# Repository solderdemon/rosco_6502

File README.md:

# Really Old-School Computer - 6502

## A 65C02 Single-Board Computer

This repository holds design files, firmware and software for the Really Old-School Computer
(6502) single-board computer, AKA the rosco_6502. This is a fully-featured, programmable,
extensible and capable 8-bit retro computer that is completely open source.

The rosco_6502 is the "little brother" of the popular [rosco_m68k](https://github.com/rosco-m68k)
m68k computer. It is made by the same people, and shares the ethos of being powerful, extensible
and above all, fun.

This project contains all the design files and source code for the project.

* All Software released under the MIT licence. See LICENSE for details.
* All Hardware released under the CERN Open Hardware licence. See LICENCE.hardware.txt.
* All Documentation released under Creative Commons Attribution. See <https://creativecommons.org/licenses/by/2.0/uk/>

## Documentation

Start with the [documentation index](docs/README.md).

* [Getting started and terminal setup](docs/getting-started.md)
* [Hardware and memory map](docs/hardware.md)
* [Building and programming ROM](docs/rom-firmware.md)
* [Building and programming PLDs](docs/pld-firmware.md)
* [Developing and loading programs](docs/software.md)
* [Troubleshooting](docs/troubleshooting.md)
* [Revision 4 notes](docs/revision-4.md)

## Specifications

### Hardware

The hardware specifications for the rosco_6502 are:

* WDC 65C02 at up-to 14MHz (In theory, 10MHz testing target currently).
* SCN68681C1A44 provides two UARTs, timers and SD Card / SPI / GPIO; the console runs at 38400 bit/s
* 528KB RAM
  * 16KB low RAM ($0000 - $3FFF)
  * 16 x 32KB RAM banks ($4000 - $BFFF)
* 8KB IO space ($C000 - $DFFF)
* 8KB or 32KB (banked) ROM $E000 - $FFFF
* High-speed decode and glue logic handled by Atmel F22V10C PLDs.
* Comprehensive expansion and IO connectors allow the system to be easily expanded!

You can see the electrical designs in [kicad](design/kicad). Programmable logic lives in [pld](code/pld).

### Software

The current firmware uses the cc65 toolchain (`ca65`, `ld65` and `da65`).
It includes hardware initialization, WozMon, SD card access, read-only FAT32
support and boot code that looks for `/ROSC0DE_6502.BIN` on the SD card.
The firmware and filesystem utilities are still under development.

See the [firmware README](code/firmware/README.md) for build
instructions.

### Related tools

* [rosco CLI](https://github.com/solderdemon/rosco-cli): a cross-platform `rosco` command
  that creates, builds and uploads rosco_6502 (and rosco_m68k) programs over UART, or
  runs them in the emulator.
* [rosco-emulator](https://github.com/solderdemon/rosco-emulator): a slimmed-down MAME
  build that emulates the rosco_6502 r4, so programs and firmware can be tested without
  the board.

See [Developing and loading programs](docs/software.md#rosco-cli-and-emulator) for usage.

## Repository layout

* [design/kicad](design/kicad): board schematics and PCB layouts.
* [code/pld](code/pld): programmable logic sources.
* [code/firmware](code/firmware): ca65 firmware and ROM linker configurations.
* [code/software](code/software): example programs, tests and filesystem utilities.
* [docs](docs): additional project documentation.

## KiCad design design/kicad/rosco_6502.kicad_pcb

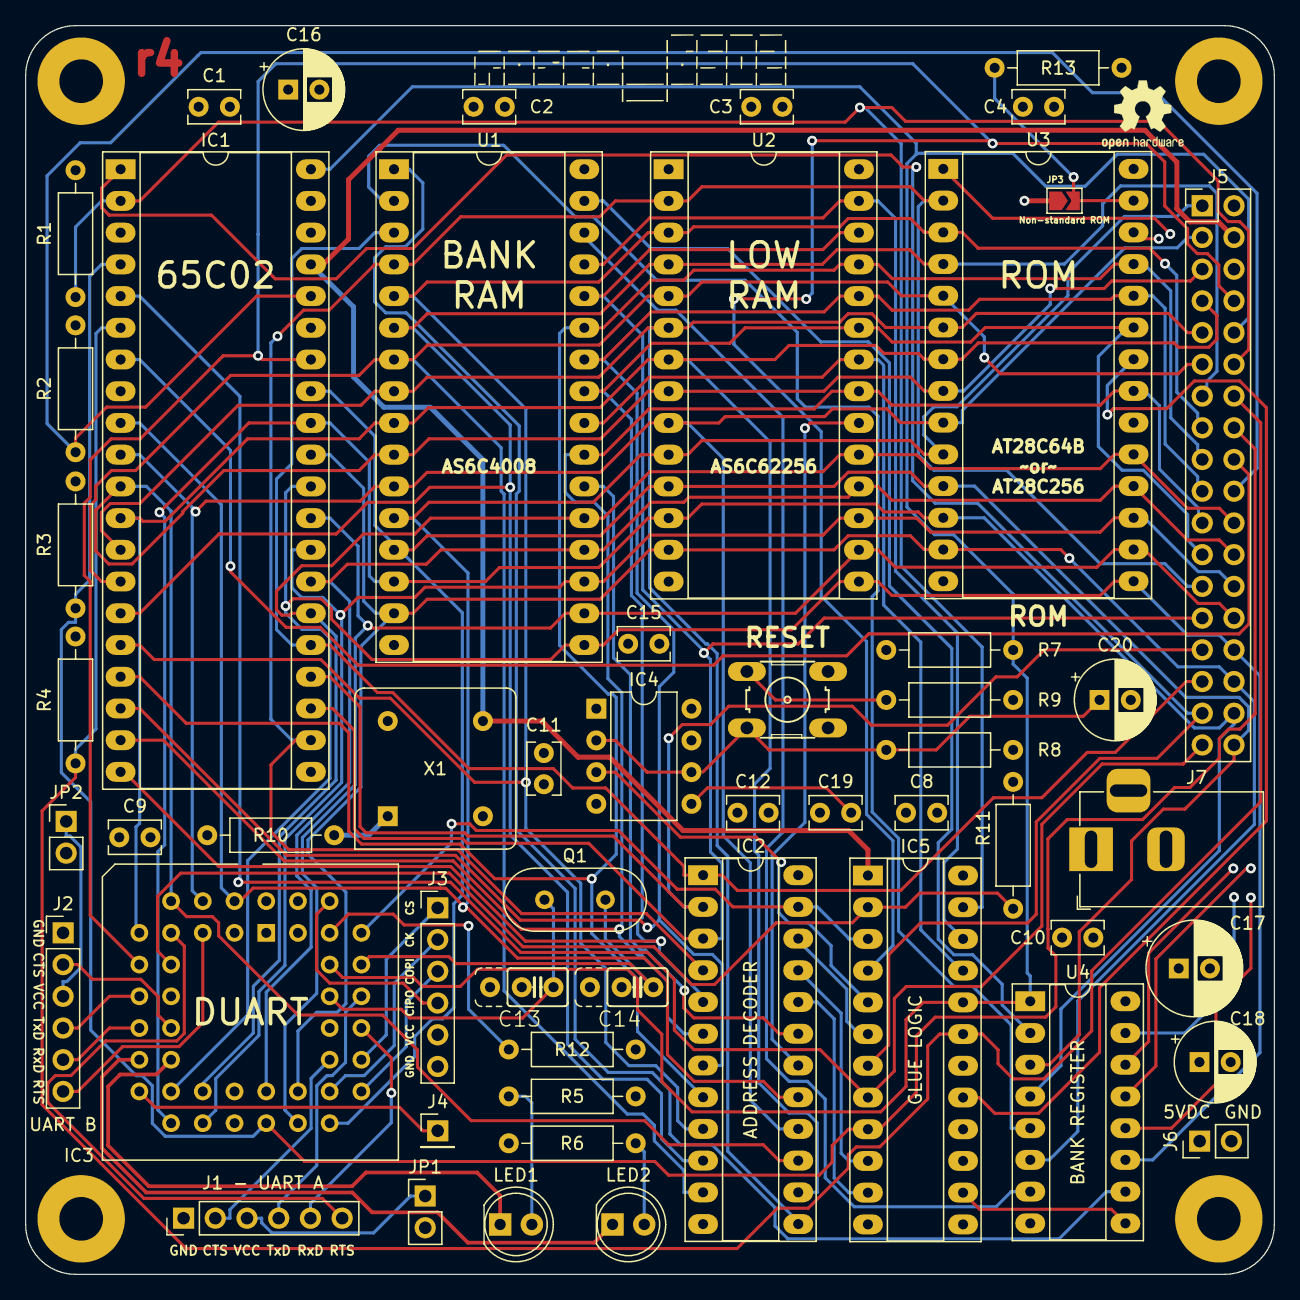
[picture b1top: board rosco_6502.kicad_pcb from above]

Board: 4 copper layers, 100.0 x 100.0 mm, 60 parts (0 on the bottom side), 81 nets.

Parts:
C1, C2, C3, C4, C8, C9, C10, C11, C12, C15, C19: 100nF; C_Rect_L4.0mm_W2.5mm_P2.50mm
C13, C14: 7pF; C2.5_or_3.5-3
C16, C18: 100uF; CP_Radial_D6.3mm_P2.50mm
C17: 470uF; CP_Radial_D7.5mm_P2.50mm
C20: 10uF; CP_Radial_D6.3mm_P2.50mm
H1, H2, H3, H4: MountingHole_Pad; MountingHole_3.5mm_Pad
IC1: W65C02SxP; DIP-40_W15.24mm_Socket_LongPads
IC2, IC5: ATF22V10C-7PX; DIP-24_W7.62mm_Socket_LongPads
IC3: XR68C681CJTR-F; PLCC-44_THT-Socket
IC4: NE555P; DIP-8_W7.62mm
J1: UART_A; PinHeader_1x06_P2.54mm_Vertical
J2: UART_B; PinHeader_1x06_P2.54mm_Vertical
J3: Conn_01x06; PinHeader_1x06_P2.54mm_Vertical
J4: Conn_01x01_Male; PinHeader_1x01_P2.54mm_Vertical
J5: Conn_02x18_Odd_Even; PinHeader_2x18_P2.54mm_Vertical
J6: Conn_01x02_Pin; PinHeader_1x02_P2.54mm_Vertical
J7: Jack-DC; BarrelJack_Horizontal
JP1, JP2: Jumper; PinHeader_1x02_P2.54mm_Vertical
JP3: SolderJumper_2_Open; SolderJumper-2_P1.3mm_Open_TrianglePad1.0x1.5mm
LED1: GREEN; LED_D5.0mm
LED2: RED; LED_D5.0mm
Q1: 3.6864MHz; Crystal_HC49-4H_Vertical
R1, R2, R3, R4, R7, R10, R11, R12, R13: 3K3; R_Axial_DIN0207_L6.3mm_D2.5mm_P10.16mm_Horizontal
R5, R6, R9: 330R; R_Axial_DIN0207_L6.3mm_D2.5mm_P10.16mm_Horizontal
R8: 2K2; R_Axial_DIN0207_L6.3mm_D2.5mm_P10.16mm_Horizontal
S1: 10-XX; B3F-10XX
U1: AS6C4008-55PCN; DIP-32_W15.24mm_Socket_LongPads
U2: AS6C62256-55PCN; DIP-28_W15.24mm_Socket_LongPads
U3: AT28C256-15PU; DIP-28_W15.24mm_Socket_LongPads
U4: 74HCT174; DIP-16_W7.62mm_Socket_LongPads
X1: 14MHz; Oscillator_DIP-8
ohw: OSHW-Logo2_7.3x6mm_SilkScreen
rosco6502: rosco_6502

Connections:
A0: IC1.9 (A0), IC2.17 (I04), IC3.2 (A1), J5.1, U1.12 (A0), U2.10 (A0), U3.10 (A0)
A1: IC1.10 (A1), IC2.16 (IO3), IC3.4 (A2), J5.3, U1.11 (A1), U2.9 (A1), U3.9 (A1)
A2: IC1.11 (A2), IC2.15 (IO2), IC3.6 (A3), J5.5, U1.10 (A2), U2.8 (A2), U3.8 (A2)
A3: IC1.12 (A3), IC2.14 (IO1), IC3.7 (A4), J5.7, U1.9 (A3), U2.7 (A3), U3.7 (A3)
A4: IC1.13 (A4), IC2.13 (I13), J5.9, U1.8 (A4), U2.6 (A4), U3.6 (A4)
A5: IC1.14 (A5), IC2.11 (I11), J5.11, U1.7 (A5), U2.5 (A5), U3.5 (A5)
A6: IC1.15 (A6), IC2.10 (I10), J5.13, U1.6 (A6), U2.4 (A6), U3.4 (A6)
A7: IC1.16 (A7), IC2.9 (I9), J5.15, U1.5 (A7), U2.3 (A7), U3.3 (A7)
A8: IC1.17 (A8), IC2.8 (I8), J5.17, U1.27 (A8), U2.25 (A8), U3.25 (A8)
A9: IC1.18 (A9), IC2.7 (I7), J5.19, U1.26 (A9), U2.24 (A9), U3.24 (A9)
A10: IC1.19 (A10), IC2.6 (I6), J5.21, U1.23 (A10), U2.21 (A10), U3.21 (A10)
A11: IC1.20 (A11), IC2.5 (I5), J5.23, U1.25 (A11), U2.23 (A11), U3.23 (A11)
A12: IC1.22 (A12), IC2.4 (I4/PD), J5.25, U1.4 (A12), U2.2 (A12), U3.2 (A12)
A13: IC1.23 (A13), IC2.3 (I3), J5.27, U1.28 (A13), U2.26 (A13)
A14: IC1.24 (A14), IC2.2 (I2), J5.29
A15: IC1.25 (A15), IC2.1 (I1/CLK), J5.31, U1.3 (A14)
BANK0: U1.31 (A15), U4.2 (Q0)
BANK1: U1.2 (A16), U4.5 (Q1)
BANK2: U1.30 (A17), U4.7 (Q2)
BANK3: U1.1 (A18), U4.10 (Q3)
BANK4: U3.26 (A13), U4.15 (Q5)
BANK5: U3.1 (A14), U4.12 (Q4)
BANKCLK: IC5.14 (IO1), U4.9 (Cp)
BANKSEL: IC2.22 (IO9), IC5.6 (I6)
BE: IC1.36 (BE), J5.20, R2.2
CLK: IC1.37 (ϕ0), IC5.1 (I1/CLK), J5.4, X1.5 (OUT)
CTSA: IC3.8 (IP0), J1.6
CTSB: IC3.5 (IP1), J2.6
D0: IC1.33 (D0), IC3.28 (D0), J5.36, U1.13 (DQ0), U2.11 (DQ0), U3.11 (DQ0), U4.3 (D0)
D1: IC1.32 (D1), IC3.18 (D1), J5.34, U1.14 (DQ1), U2.12 (DQ1), U3.12 (DQ1), U4.4 (D1)
D2: IC1.31 (D2), IC3.27 (D2), J5.32, U1.15 (DQ2), U2.13 (DQ2), U3.13 (DQ2), U4.6 (D2)
D3: IC1.30 (D3), IC3.19 (D3), J5.30, U1.17 (DQ3), U2.15 (DQ3), U3.15 (DQ3), U4.11 (D3)
D4: IC1.29 (D4), IC3.26 (D4), J5.28, U1.18 (DQ4), U2.16 (DQ4), U3.16 (DQ4), U4.14 (D5)
D5: IC1.28 (D5), IC3.20 (D5), J5.26, U1.19 (DQ5), U2.17 (DQ5), U3.17 (DQ5), U4.13 (D4)
D6: IC1.27 (D6), IC3.25 (D6), J5.24, U1.20 (DQ6), U2.18 (DQ6), U3.18 (DQ6)
D7: IC1.26 (D7), IC3.21 (D7), J5.22, U1.21 (DQ7), U2.19 (DQ7), U3.19 (DQ7)
GND: C1.1, C2.1, C3.1, C4.1, C8.1, C9.1, C10.1, C11.1, C12.1, C13.1, C14.1, C15.1, C16.2, C17.2, C18.2, C20.2, H1.1, H2.1, H3.1, H4.1, IC1.21 (VSS), IC2.12 (GND), IC3.3 (IP3), IC3.22 (GND), IC4.1 (GND), IC5.12 (GND), J1.1, J2.1, J3.6, J5.6, J6.2, J7.2, JP3.1 (A), R9.2, U1.16 (VSS), U2.1 (A14), U2.14 (VSS), U3.14 (VSS), U3.20 (CE#), U4.8 (GND), X1.4 (GND)
HWRST: IC4.3 (Q), IC5.5 (I5)
IRQ: IC1.4 (~IRQ), IC3.24 (INTR), IC5.9 (I9), J5.16, R3.2
NMI: IC1.6 (~NMI), IC5.19 (IO6), J5.14, R4.2
unnamed: IC3.41 (*IACK), R12.2
unnamed: IC3.15 (OP3), LED2.1 (K)
unnamed: IC3.16 (OP5), LED1.1 (K)
unnamed: C13.2, IC3.36 (X1/CLK), Q1.1
unnamed: C14.2, IC3.37 (X2), Q1.2
unnamed: C19.2, IC4.5 (CV)
unnamed: C20.1, IC4.2 (TR), IC4.6 (THR), R8.1, S1.3
unnamed: JP3.2 (B), R13.1, U3.27 (WE#)
unnamed: LED1.2 (A), R5.1
unnamed: LED2.2 (A), R6.2
unnamed: R9.1, S1.1 (S)
unnamed: R10.2, X1.1 (EN)
RDY: IC1.2 (RDY), IC5.23 (IO10), J5.12, R1.2
RTSA: IC3.32 (OP0), J1.2
RTSB: IC3.14 (OP1), J2.2
RXDA: IC3.35 (RXDA), J1.4
RXDB: IC3.11 (RXDB), J2.4
R/~W: IC1.34 (R/~W), IC3.9 (*R/*W), IC5.4 (I4/PD), J5.8
SPICLK: IC3.30 (OP4), J3.2
SPICS: IC3.31 (OP2), J3.1
SPICS2: IC3.17 (OP7), J4.1
SPIMISO: IC3.40 (IP2), J3.4
SPIMOSI: IC3.29 (OP6), J3.3
SYNC: IC1.7 (SYNC), J5.18
TXDA: IC3.33 (TXDA), J1.5
TXDB: IC3.13 (TXDB), J2.5
VCC: C1.2, C2.2, C3.2, C4.2, C8.2, C9.2, C10.2, C11.2, C12.2, C15.2, C16.1, C17.1, C18.1, C19.1, IC1.8 (VDD), IC1.38 (~SO), IC2.24 (VCC), IC3.44 (VCC), IC4.4 (R), IC4.8 (VCC), IC5.24 (VCC), J3.5, J5.2, J6.1, J7.1, JP1.2 (B), JP2.2 (B), R1.1, R2.1, R3.1, R4.1, R5.2, R6.1, R7.1, R8.2, R10.1, R11.1, R12.1, R13.2, U1.32 (VCC), U2.28 (VCC), U3.28 (VCC), U4.16 (VCC), X1.8 (Vcc)
VCCUA: J1.3, JP1.1 (A)
VCCUB: J2.3, JP2.1 (A)
~BANKRAM: IC2.19 (IO6), U1.22 (CE#)
~DUADTACK: IC3.10 (*DTALK), IC5.2 (I2), R11.2
~DUASEL: IC2.23 (IO10), IC3.39 (CS), IC5.3 (I3)
~IO: IC2.20 (IO7), IC5.11 (I11)
~LOWRAM: IC2.18 (IO5), U2.20 (CE#)
~ML: IC1.5 (~ML), IC5.8 (I8), J5.35
~RD: IC5.21 (IO8), U1.24 (OE#), U2.22 (OE#)
~RESET: IC1.40 (~RES), IC3.38 (*RESET), IC5.20 (IO7), J5.10, R7.2, U4.1 (~Mr)
~ROMOE: IC5.17 (I04), U3.22 (OE#)
~ROM: IC2.21 (IO8), IC5.10 (I10)
~VP: IC1.1 (~VP), IC5.7 (I7), J5.33
~WR: IC5.22 (IO9), U1.29 (WE#), U2.27 (WE#)

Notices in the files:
design/kicad/rosco_6502.kicad_pcb:
Copyright (c)2022-2023 Ross Bamford & Contributors
Open Source Hardware (CERN OHL)
